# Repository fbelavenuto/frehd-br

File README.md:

# TRS-80 FreHD BR version

### English

FreHD is a HD emulator for TRS-80 classic computer.

This board is my version made in Cadsoft Eagle software. Original project:

http://members.iinet.net.au/~ianmav/trs80/emulator.htm

`FreHD` is the project itself, `CP300_Adapter` is for Brazilian TRS-80 Model III clone

### Português

FreHD é um emulador de HD para computadores TRS-80.

Estas placas são uma versão minha feito no software Autodesk Eagle. Projeto original:

http://members.iinet.net.au/~ianmav/trs80/emulator.htm

`FreHD` é o projeto em si, `CP300_Adapter` é para o clone brasileiro TRS-80 model III.

Este projeto utiliza um microcontrolador PIC que deve ser gravado com o firmware do arquivo `FreHD_213.hex` e utiliza um circuito integrado de lógica programável (GAL) que deve ser gravado com o arquivo `gal16v8.jed`.

Para o clone CP500 é necessário a regravação da EPROM interna ou troca com o conteúdo do arquivo `CP500_FreHD.rom`.

Para o CP300 é necessário a construção do adaptador que contém uma EPROM que deve ser gravada com o conteúdo do arquivo `FreHD(3000).bin`. A EPROM utilizada é a 2732 que tem espaço para 4KBytes de dados, por ser mais fácil de se encontrar. O arquivo contém somente 2KBytes de dados e deve ser gravado no começo da EPROM (offset 0) deixando o restante da EPROM sem conteúdo.

A lista de material pode ser encontrada em formato Markdown na pasta *Doc* de cada projeto.

É necessário a confecção de um cabo multivias com 50 vias/conector 2x25 para ligação entre o FreHD e Micro (ou Adaptador) e um cabo multivias de 34 vias/conector 2x17 para a ligação do adaptador no CP300. O cabo de 50 vias pode ser aproveitado de antigos cabos SCSI e para o cabo de 34 vias pode ser aproveitado cabos de floppy sem a torção.

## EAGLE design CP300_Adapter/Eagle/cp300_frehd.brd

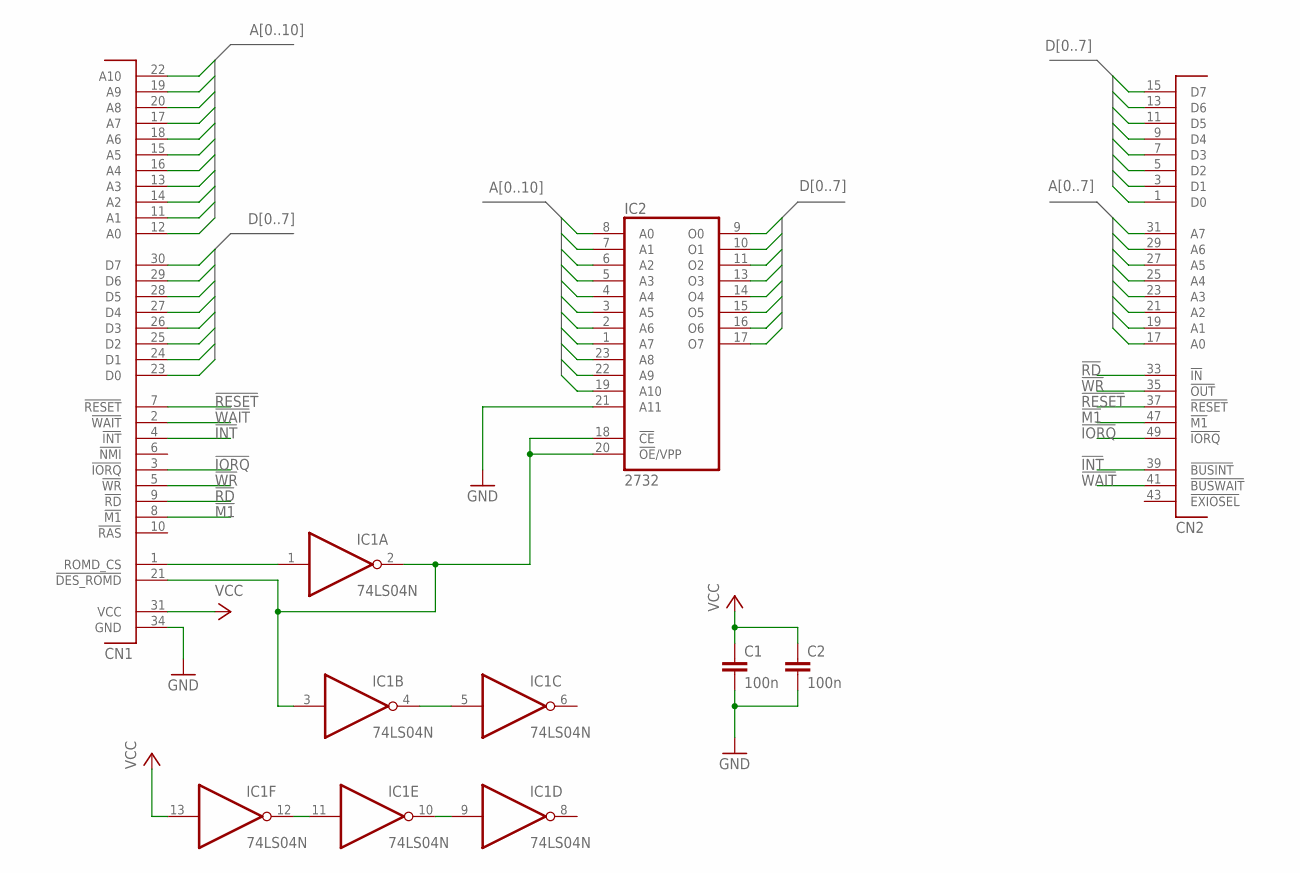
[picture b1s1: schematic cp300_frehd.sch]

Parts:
C1, C2: 100n; C050-024X044
CN1: CP300_EXPA; 2X17
CN2: TRS80_EXPA; 2X25
IC1: 74LS04N; DIL14
IC2: 2732; DIL24

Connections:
!INT: CN1.4 (!INT), CN2.39 (!BUSINT)
!IORQ: CN1.3 (!IORQ), CN2.49 (!IORQ)
!M1: CN1.8 (!M1), CN2.47 (!M1)
!RD: CN1.9 (!RD), CN2.33 (!IN)
!RESET: CN1.7 (!RESET), CN2.37 (!RESET)
!WAIT: CN1.2 (!WAIT), CN2.41 (!BUSWAIT)
!WR: CN1.5 (!WR), CN2.35 (!OUT)
A0: CN1.12 (A0), CN2.17 (A0), IC2.8 (A0)
A1: CN1.11 (A1), CN2.19 (A1), IC2.7 (A1)
A2: CN1.14 (A2), CN2.21 (A2), IC2.6 (A2)
A3: CN1.13 (A3), CN2.23 (A3), IC2.5 (A3)
A4: CN1.16 (A4), CN2.25 (A4), IC2.4 (A4)
A5: CN1.15 (A5), CN2.27 (A5), CN2.29 (A6), IC2.3 (A5)
A6: CN1.18 (A6), IC2.2 (A6)
A7: CN1.17 (A7), CN2.31 (A7), IC2.1 (A7)
A8: CN1.20 (A8), IC2.23 (A8)
A9: CN1.19 (A9), IC2.22 (A9)
A10: CN1.22 (A10), IC2.19 (A10)
D0: CN1.23 (D0), CN2.1 (D0), IC2.9 (O0)
D1: CN1.24 (D1), CN2.3 (D1), IC2.10 (O1)
D2: CN1.25 (D2), CN2.5 (D2), IC2.11 (O2)
D3: CN1.26 (D3), CN2.7 (D3), IC2.13 (O3)
D4: CN1.27 (D4), CN2.9 (D4), IC2.14 (O4)
D5: CN1.28 (D5), CN2.11 (D5), IC2.15 (O5)
D6: CN1.29 (D6), CN2.13 (D6), IC2.16 (O6)
D7: CN1.30 (D7), CN2.15 (D7), IC2.17 (O7)
GND: C1.2, C2.2, CN1.34 (GND), CN2.2 (GND), CN2.4 (GND), CN2.6 (GND), CN2.8 (GND), CN2.10 (GND), CN2.12 (GND), CN2.14 (GND), CN2.16 (GND), CN2.18 (GND), CN2.20 (GND), CN2.22 (GND), CN2.24 (GND), CN2.26 (GND), CN2.28 (GND), CN2.30 (GND), CN2.32 (GND), CN2.34 (GND), CN2.36 (GND), CN2.38 (GND), CN2.40 (GND), CN2.42 (GND), CN2.44 (GND), CN2.46 (GND), CN2.48 (GND), CN2.50 (GND), IC1.7 (GND), IC2.12 (GND), IC2.21 (A11)
unnamed: IC1.11 (I), IC1.12 (O)
unnamed: IC1.9 (I), IC1.10 (O)
unnamed: IC1.4 (O), IC1.5 (I)
unnamed: CN1.1 (ROMD_CS), IC1.1 (I)
unnamed: CN1.21 (!DES_ROMD), IC1.2 (O), IC1.3 (I), IC2.18 (!CE), IC2.20 (!OE!/VPP)
VCC: C1.1, C2.1, CN1.31 (VCC), IC1.13 (I), IC1.14 (VCC), IC2.24 (VCC)

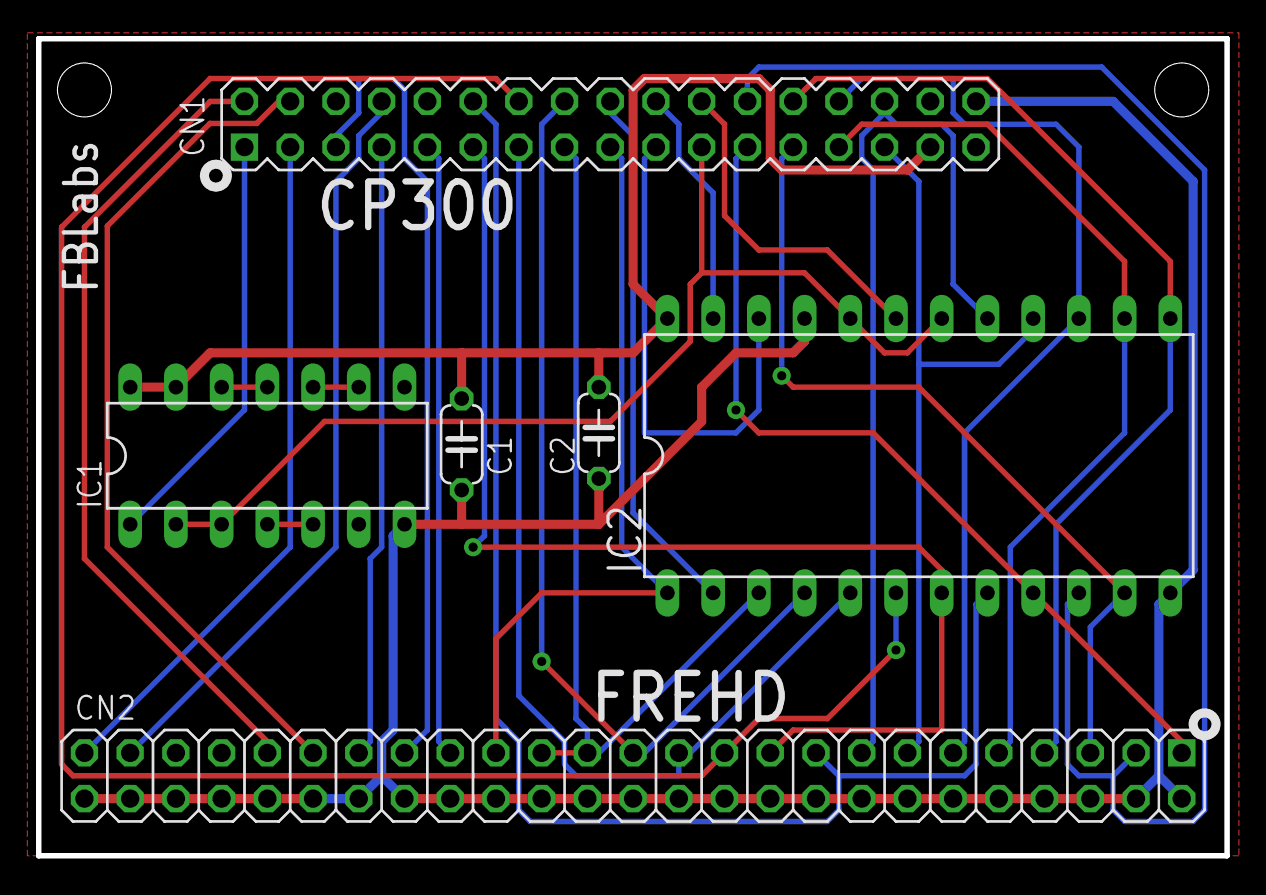
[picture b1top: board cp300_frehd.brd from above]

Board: 2 copper layers, 66.0 x 45.4 mm, 6 parts (0 on the bottom side), 33 nets.

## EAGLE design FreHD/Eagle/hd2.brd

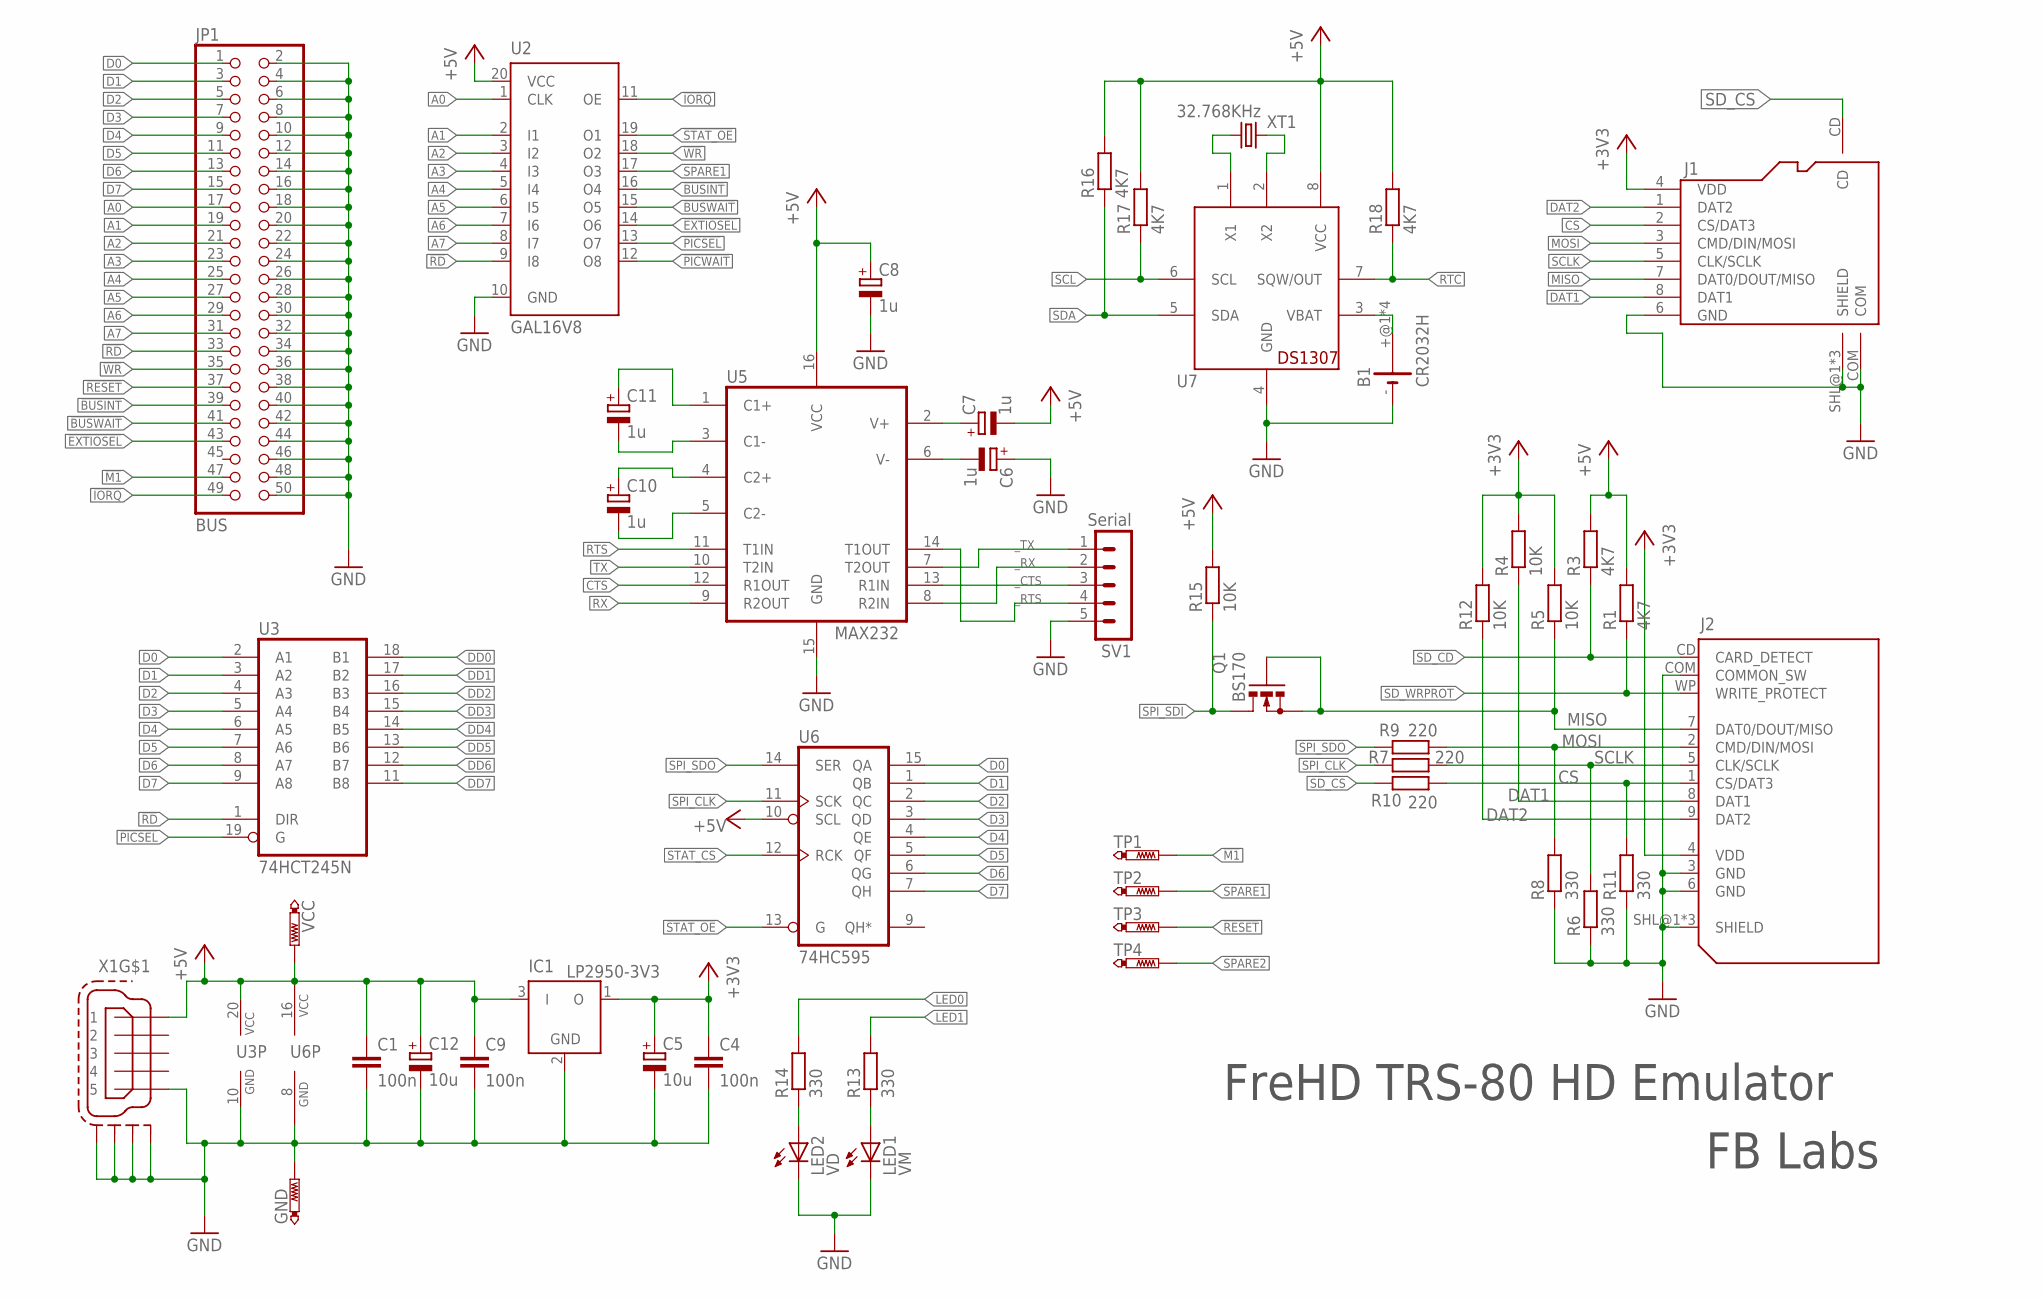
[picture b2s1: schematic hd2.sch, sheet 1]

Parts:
B1: CR2032H
C1, C4, C9: 100n; C050-024X044
C5, C12: 10u; E2-4
C6, C7, C8, C10, C11: 1u; E2-4
GND: PTR1B2,54; B2,54
IC1: LP2950-3V3; TO92
J1: MICROSD-9P; 9P-SMD-W/-RING
J2: SDMMC06132; 06132
JP1: BUS; 2X25
LED1: VM; LED3MM
LED2: VD; LED3MM
Q1: BS170; SOT54E
R1, R3, R16, R17, R18: 4K7; 0207/10
R4, R5, R12, R15: 10K; 0207/10
R6, R8, R11, R13, R14: 330; 0207/10
R7, R9, R10: 220; 0207/10
SV1: Serial; MA05-1
TP1, TP2, TP3, TP4: PTR1PAD1-10; P1-10
U2: GAL16V8; DIL20
U3: 74HCT245N; DIL20
U5: MAX232; DIL16
U6: 74HC595; DIL16
U7: DS1307; DIL08
VCC: PTR1B2,54; B2,54
X1: MINI-USB-SCHIELD-32005-301; 32005-301
XT1: 32.768KHz; TC26V

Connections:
!BUSINT: JP1.39, U2.16 (O4)
!BUSWAIT: JP1.41, U2.15 (O5)
!EXTIOSEL: JP1.43, U2.14 (O6)
!IORQ: JP1.49, U2.11 (OE)
!M1: JP1.47, TP1.TP
!PICSEL: U2.13 (O7), U3.19 (G); also elsewhere on the board
!PICWAIT: U2.12 (O8); also elsewhere on the board
!RD: JP1.33, U2.9 (I8), U3.1 (DIR); also elsewhere on the board
!RESET: JP1.37, TP3.TP
!STAT_OE: U2.19 (O1), U6.13 (G)
!WR: JP1.35, U2.18 (O2)
+3V3: C4.1, C5.+, IC1.1 (O), J1.4 (VDD), J2.4 (VDD), R4.2, R5.2, R12.2
+5V: C1.1, C7.-, C8.+, C9.1, C12.+, IC1.3 (I), R1.2, R3.2, R15.2, R16.2, R17.2, R18.2, U2.20 (VCC), U3.20 (VCC), U5.16 (VCC), U6.10 (SCL), U6.16 (VCC), U7.8 (VCC), VCC.TP, X1.1; also elsewhere on the board
A0: JP1.17, U2.1 (CLK); also elsewhere on the board
A1: JP1.19, U2.2 (I1); also elsewhere on the board
A2: JP1.21, U2.3 (I2); also elsewhere on the board
A3: JP1.23, U2.4 (I3); also elsewhere on the board
A4: JP1.25, U2.5 (I4)
A5: JP1.27, U2.6 (I5)
A6: JP1.29, U2.7 (I6)
A7: JP1.31, U2.8 (I7)
CS: J1.2 (CS/DAT3), J2.1 (CS/DAT3), R10.1, R11.2
CTS: U5.12 (R1OUT); also elsewhere on the board
D0: JP1.1, U3.2 (A1), U6.15 (QA)
D1: JP1.3, U3.3 (A2), U6.1 (QB)
D2: JP1.5, U3.4 (A3), U6.2 (QC)
D3: JP1.7, U3.5 (A4), U6.3 (QD)
D4: JP1.9, U3.6 (A5), U6.4 (QE)
D5: JP1.11, U3.7 (A6), U6.5 (QF)
D6: JP1.13, U3.8 (A7), U6.6 (QG)
D7: JP1.15, U3.9 (A8), U6.7 (QH)
DAT1: J1.8 (DAT1), J2.8 (DAT1), R4.1
DAT2: J1.1 (DAT2), J2.9 (DAT2), R12.1
DD0: U3.18 (B1); also elsewhere on the board
DD1: U3.17 (B2); also elsewhere on the board
DD2: U3.16 (B3); also elsewhere on the board
DD3: U3.15 (B4); also elsewhere on the board
DD4: U3.14 (B5); also elsewhere on the board
DD5: U3.13 (B6); also elsewhere on the board
DD6: U3.12 (B7); also elsewhere on the board
DD7: U3.11 (B8); also elsewhere on the board
GND: B1.-, C1.2, C4.2, C5.-, C6.+, C8.-, C9.2, C12.-, GND.TP, IC1.2 (GND), J1.6 (GND), J1.COM, J1.SHL@1 (SHIELD), J1.SHL@2 (SHIELD), J1.SHL@3 (SHIELD), J2.3 (GND), J2.6 (GND), J2.COM (COMMON_SW), J2.SHL@1 (SHIELD), J2.SHL@2 (SHIELD), J2.SHL@3 (SHIELD), JP1.2, JP1.4, JP1.6, JP1.8, JP1.10, JP1.12, JP1.14, JP1.16, JP1.18, JP1.20, JP1.22, JP1.24, JP1.26, JP1.28, JP1.30, JP1.32, JP1.34, JP1.36, JP1.38, JP1.40, JP1.42, JP1.44, JP1.46, JP1.48, JP1.50, LED1.K (C), LED2.K (C), R6.1, R8.1, R11.1, SV1.5, U2.10 (GND), U3.10 (GND), U5.15 (GND), U6.8 (GND), U7.4 (GND), X1.5, X1.M1 (S1), X1.M2 (S2), X1.M3 (S3), X1.M4 (S4); also elsewhere on the board
LED0: R14.2; also elsewhere on the board
LED1: R13.2; also elsewhere on the board
MISO: J1.7 (DAT0/DOUT/MISO), J2.7 (DAT0/DOUT/MISO), Q1.G, Q1.S, R5.1
MOSI: J1.3 (CMD/DIN/MOSI), J2.2 (CMD/DIN/MOSI), R8.2, R9.1
unnamed: U7.1 (X1), XT1.1
unnamed: U7.2 (X2), XT1.2
unnamed: C6.-, U5.6 (V-)
unnamed: C7.+, U5.2 (V+)
unnamed: B1.+@1 (+), B1.+@2 (+), B1.+@3 (+), B1.+@4 (+), U7.3 (VBAT)
unnamed: C11.-, U5.3 (C1-)
unnamed: C11.+, U5.1 (C1+)
unnamed: C10.+, U5.4 (C2+)
unnamed: C10.-, U5.5 (C2-)
unnamed: LED2.A, R14.1
unnamed: LED1.A, R13.1
RTC: R18.1, U7.7 (SQW/OUT); also elsewhere on the board
RTS: U5.11 (T1IN); also elsewhere on the board
RX: U5.9 (R2OUT); also elsewhere on the board
SCL: R17.1, U7.6 (SCL); also elsewhere on the board
SCLK: J1.5 (CLK/SCLK), J2.5 (CLK/SCLK), R6.2, R7.1
SDA: R16.1, U7.5 (SDA); also elsewhere on the board
SD_CD: J2.CD (CARD_DETECT), R3.1; also elsewhere on the board
SD_CS: J1.CD, R10.2; also elsewhere on the board
SD_WRPROT: J2.WP (WRITE_PROTECT), R1.1; also elsewhere on the board
SPARE1: TP2.TP, U2.17 (O3); also elsewhere on the board
SPARE2: TP4.TP; also elsewhere on the board
SPI_CLK: R7.2, U6.11 (SCK); also elsewhere on the board
SPI_SDI: Q1.D, R15.1; also elsewhere on the board
SPI_SDO: R9.2, U6.14 (SER); also elsewhere on the board
STAT_CS: U6.12 (RCK); also elsewhere on the board
TX: U5.10 (T2IN); also elsewhere on the board
_CTS: SV1.3, U5.13 (R1IN)
_RTS: SV1.4, U5.14 (T1OUT)
_RX: SV1.2, U5.8 (R2IN)
_TX: SV1.1, U5.7 (T2OUT)

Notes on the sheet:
FreHD TRS-80 HD Emulator
FB Labs

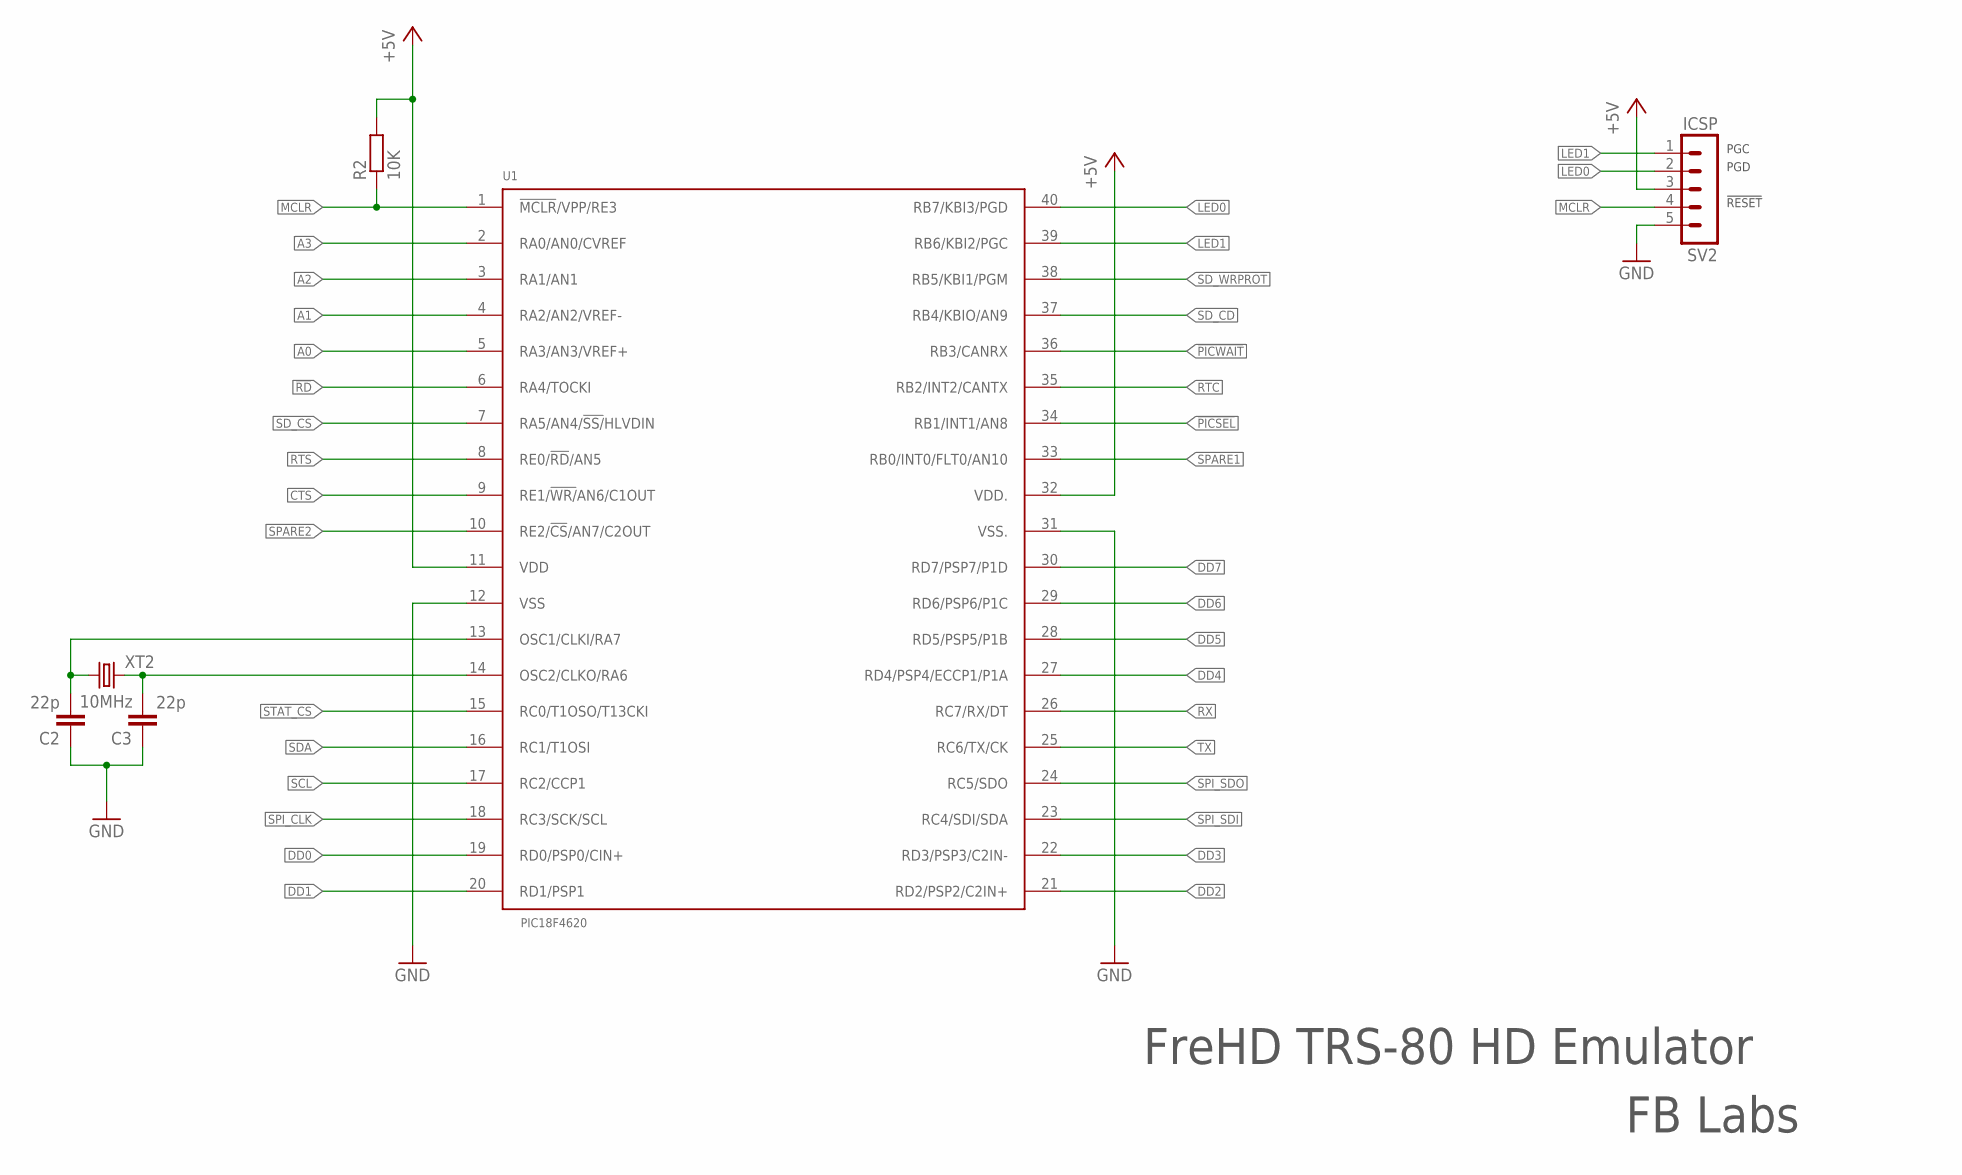
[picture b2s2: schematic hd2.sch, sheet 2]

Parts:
C2, C3: 22p; C050-024X044
R2: 10K; 0207/10
SV2: ICSP; MA05-1
U1: PIC18F4620; PDIP-40
XT2: 10MHz; HC49U-V

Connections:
!PICSEL: U1.34 (RB1/INT1/AN8); also elsewhere on the board
!PICWAIT: U1.36 (RB3/CANRX); also elsewhere on the board
!RD: U1.6 (RA4/TOCKI); also elsewhere on the board
+5V: R2.2, SV2.3, U1.11 (VDD), U1.32 (VDD.); also elsewhere on the board
A0: U1.5 (RA3/AN3/VREF+); also elsewhere on the board
A1: U1.4 (RA2/AN2/VREF-); also elsewhere on the board
A2: U1.3 (RA1/AN1); also elsewhere on the board
A3: U1.2 (RA0/AN0/CVREF); also elsewhere on the board
CTS: U1.9 (RE1/!WR/!AN6/C1OUT); also elsewhere on the board
DD0: U1.19 (RD0/PSP0/CIN+); also elsewhere on the board
DD1: U1.20 (RD1/PSP1); also elsewhere on the board
DD2: U1.21 (RD2/PSP2/C2IN+); also elsewhere on the board
DD3: U1.22 (RD3/PSP3/C2IN-); also elsewhere on the board
DD4: U1.27 (RD4/PSP4/ECCP1/P1A); also elsewhere on the board
DD5: U1.28 (RD5/PSP5/P1B); also elsewhere on the board
DD6: U1.29 (RD6/PSP6/P1C); also elsewhere on the board
DD7: U1.30 (RD7/PSP7/P1D); also elsewhere on the board
GND: C2.1, C3.1, SV2.5, U1.12 (VSS), U1.31 (VSS.); also elsewhere on the board
LED0: SV2.2, U1.40 (RB7/KBI3/PGD); also elsewhere on the board
LED1: SV2.1, U1.39 (RB6/KBI2/PGC); also elsewhere on the board
MCLR: R2.1, SV2.4, U1.1 (!MCLR!/VPP/RE3)
unnamed: C2.2, U1.13 (OSC1/CLKI/RA7), XT2.1
unnamed: C3.2, U1.14 (OSC2/CLKO/RA6), XT2.2
RTC: U1.35 (RB2/INT2/CANTX); also elsewhere on the board
RTS: U1.8 (RE0/!RD!/AN5); also elsewhere on the board
RX: U1.26 (RC7/RX/DT); also elsewhere on the board
SCL: U1.17 (RC2/CCP1); also elsewhere on the board
SDA: U1.16 (RC1/T1OSI); also elsewhere on the board
SD_CD: U1.37 (RB4/KBIO/AN9); also elsewhere on the board
SD_CS: U1.7 (RA5/AN4/!SS/!HLVDIN); also elsewhere on the board
SD_WRPROT: U1.38 (RB5/KBI1/PGM); also elsewhere on the board
SPARE1: U1.33 (RB0/INT0/FLT0/AN10); also elsewhere on the board
SPARE2: U1.10 (RE2/!CS!/AN7/C2OUT); also elsewhere on the board
SPI_CLK: U1.18 (RC3/SCK/SCL); also elsewhere on the board
SPI_SDI: U1.23 (RC4/SDI/SDA); also elsewhere on the board
SPI_SDO: U1.24 (RC5/SDO); also elsewhere on the board
STAT_CS: U1.15 (RC0/T1OSO/T13CKI); also elsewhere on the board
TX: U1.25 (RC6/TX/CK); also elsewhere on the board

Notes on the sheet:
PGD
PGC
!RESET
FreHD TRS-80 HD Emulator
FB Labs

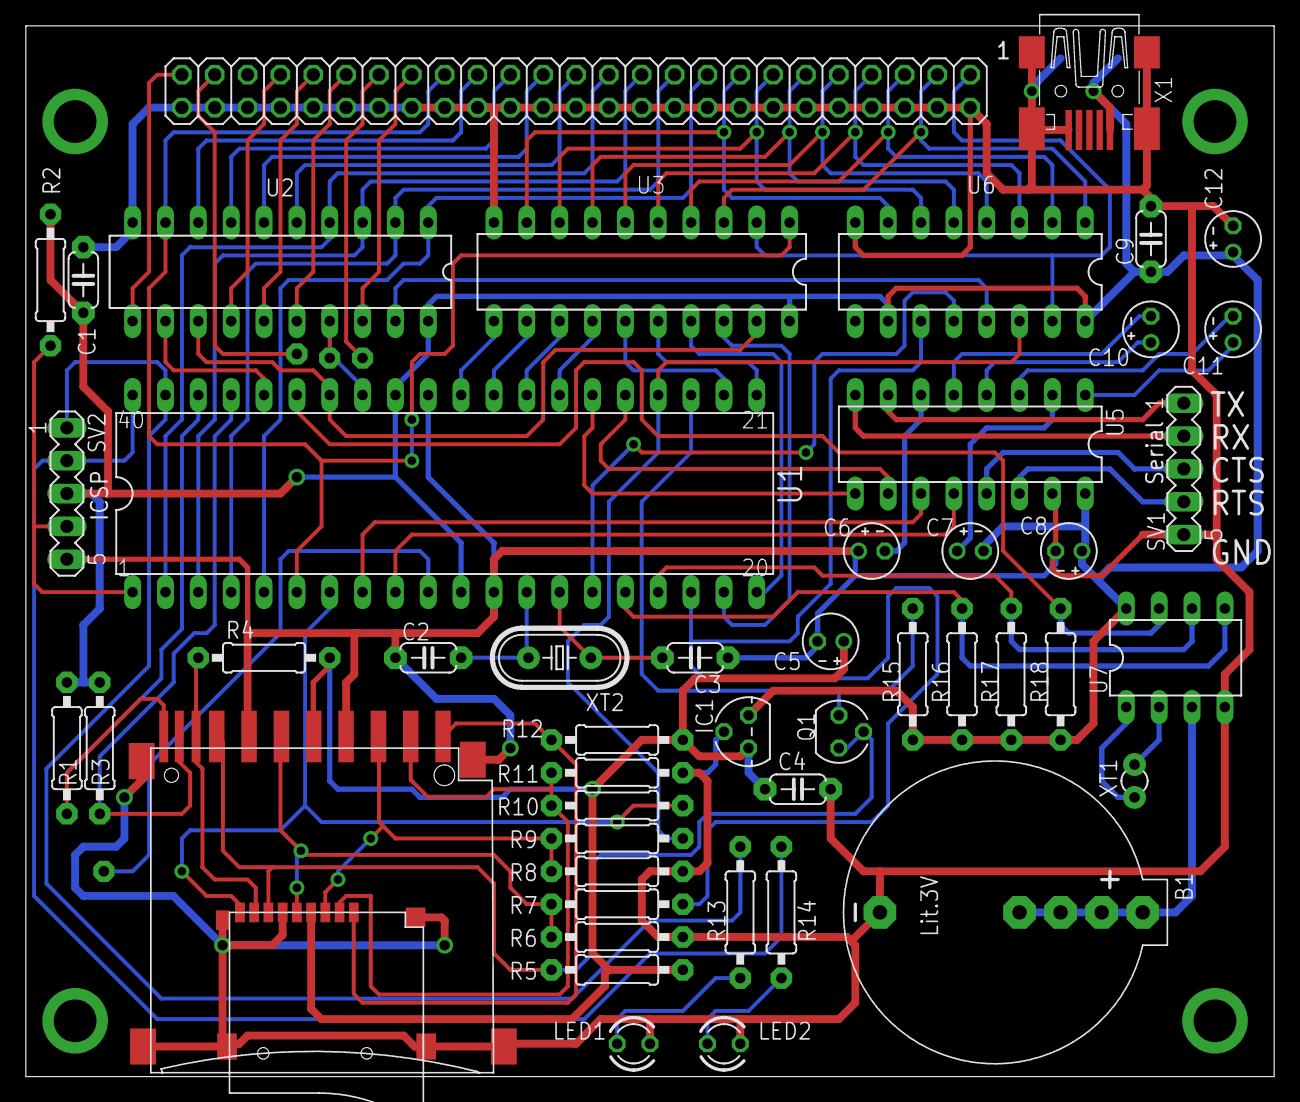
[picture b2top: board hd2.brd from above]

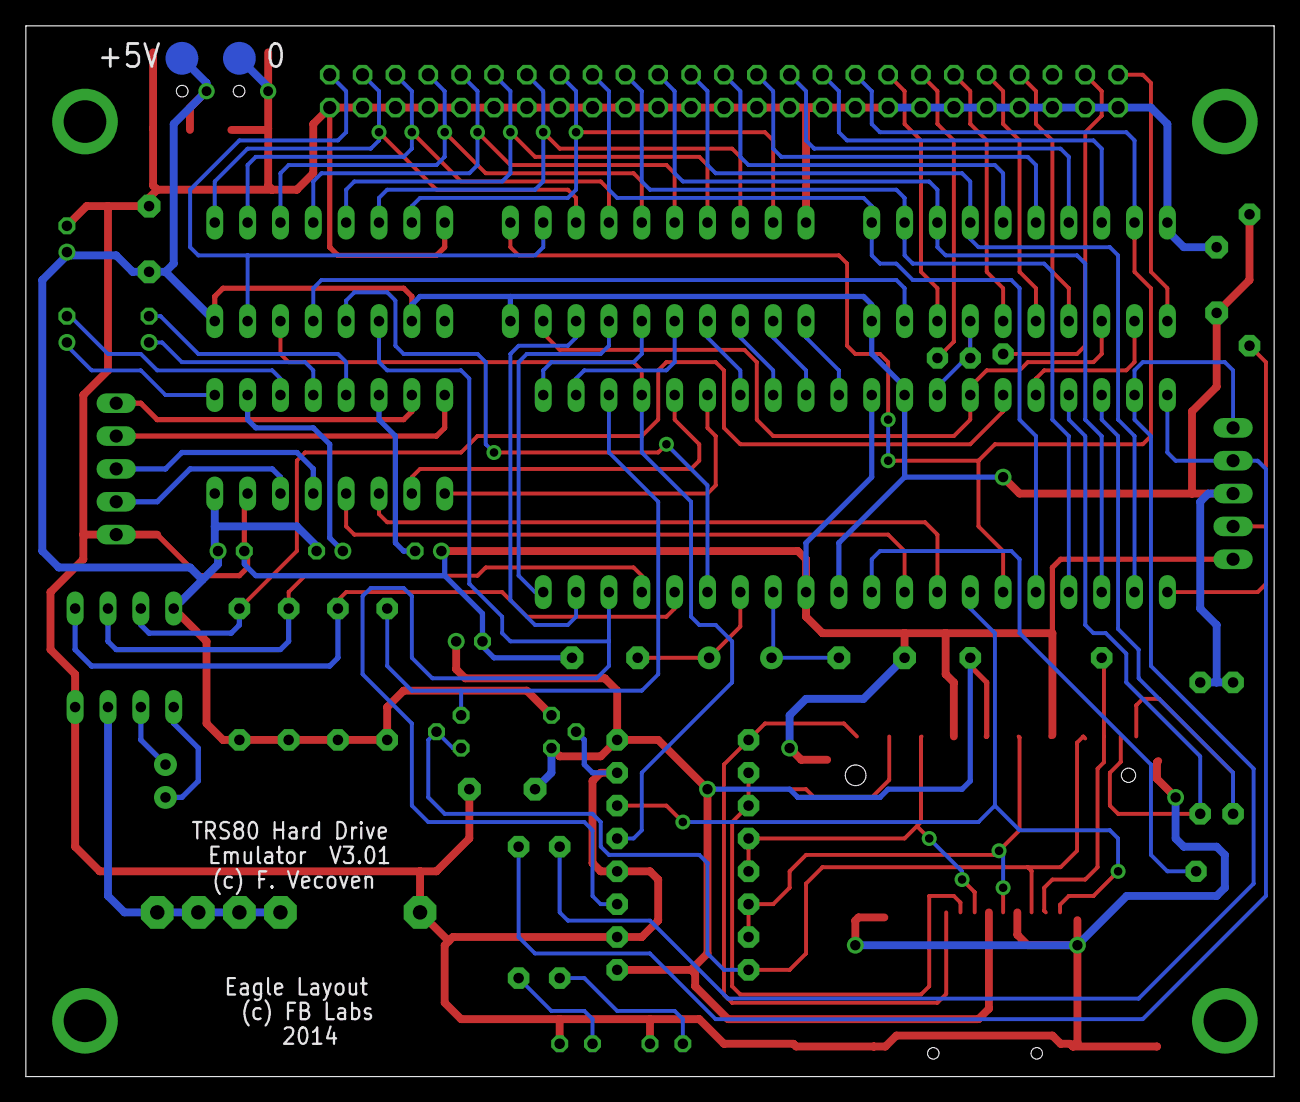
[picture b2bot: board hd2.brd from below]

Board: 2 copper layers, 96.5 x 81.2 mm, 55 parts (2 on the bottom side), 80 nets.

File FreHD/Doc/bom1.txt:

Part Value       Device          Package      Description

U1   PIC18F4620  PIC18F4680      PDIP-40
U2   GAL16V8     ATF16V8BP3      DIL20        High perfomance CMOS (electrically erasable) programmable logic device (PLD)
U3   74HCT245N   74HCT245N       DIL20        Octal BUS TRANSCEIVER, 3-state
U5   MAX232      MAX232PTH       DIL16        RS232 Transceiver
U6   74HC595N    74HC595N        DIL16        8-bit SHIFT REGISTER, output latch
U7   DS1307      DS1307          DIL08        DS1307
IC1  LP2950-3V3  LP2950Z         TO92         100 mA, Low Power Low Dropout Voltage Regulator
Q1   BS170       BS170           SOT54E       N-CHANNEL MOS FET
J1   MICROSD     MICROSD         MICROSD      Micro SD Socket (optional)
J2   SDMMC06132  SDMMC06132      06132        SD MMC Card holder
XT1  32.768KHz   CRYSTALTC26V    TC26V        CRYSTAL
XT2  10MHz       CRYSTALHC49U-V  HC49U-V      CRYSTAL
B1   CR2032H     CR2032H         CR2032H      LI BATTERY Varta
C1   100n        C-EU050-024X044 C050-024X044 CAPACITOR, European symbol
C2   22p         C-EU050-024X044 C050-024X044 CAPACITOR, European symbol
C3   22p         C-EU050-024X044 C050-024X044 CAPACITOR, European symbol
C4   100n        C-EU050-024X044 C050-024X044 CAPACITOR, European symbol
C5   10u         CPOL-EUE2-4     E2-4         POLARIZED CAPACITOR, European symbol
C6   1u          CPOL-EUE2-4     E2-4         POLARIZED CAPACITOR, European symbol
C7   1u          CPOL-EUE2-4     E2-4         POLARIZED CAPACITOR, European symbol
C8   1u          CPOL-EUE2-4     E2-4         POLARIZED CAPACITOR, European symbol
C9   100n        C-EU050-024X044 C050-024X044 CAPACITOR, European symbol
C10  1u          CPOL-EUE2-4     E2-4         POLARIZED CAPACITOR, European symbol
C11  1u          CPOL-EUE2-4     E2-4         POLARIZED CAPACITOR, European symbol
C12  10u         CPOL-EUE2-4     E2-4         POLARIZED CAPACITOR, European symbol
R1   4K7         R-EU_0207/10    0207/10      RESISTOR, European symbol
R2   10K         R-EU_0207/10    0207/10      RESISTOR, European symbol
R3   4K7         R-EU_0207/10    0207/10      RESISTOR, European symbol
R4   10K         R-EU_0207/10    0207/10      RESISTOR, European symbol
R5   10K         R-EU_0207/10    0207/10      RESISTOR, European symbol
R6   330         R-EU_0207/10    0207/10      RESISTOR, European symbol
R7   220         R-EU_0207/10    0207/10      RESISTOR, European symbol
R8   330         R-EU_0207/10    0207/10      RESISTOR, European symbol
R9   220         R-EU_0207/10    0207/10      RESISTOR, European symbol
R10  220         R-EU_0207/10    0207/10      RESISTOR, European symbol
R11  330         R-EU_0207/10    0207/10      RESISTOR, European symbol
R12  10K         R-EU_0207/10    0207/10      RESISTOR, European symbol
R13  330         R-EU_0207/10    0207/10      RESISTOR, European symbol
R14  330         R-EU_0207/10    0207/10      RESISTOR, European symbol
R15  10K         R-EU_0207/10    0207/10      RESISTOR, European symbol
R16  4K7         R-EU_0207/10    0207/10      RESISTOR, European symbol
R17  4K7         R-EU_0207/10    0207/10      RESISTOR, European symbol
R18  4K7         R-EU_0207/10    0207/10      RESISTOR, European symbol
X1   MUSB-B      MiniUSB type B  M-USB B      Mini USB type B connector
JP1  BUS         PINHD-2X25      2X25         PIN HEADER
SV1  Serial      MA05-1          MA05-1       PIN HEADER
SV2  ICSP        MA05-1          MA05-1       PIN HEADER
LED1 VM          LED3MM          LED3MM       LED Red 3mm
LED2 VD          LED3MM          LED3MM       LED Green 3mm

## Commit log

2021-04-29 Corrigindo gitignore e adicionado arquivos de furação Gerber
2021-05-01 Adicionado documentação e lista de materiais

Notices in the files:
parts and their libraries:
SparkFun: Licensing: CC v3.0 Share-Alike You are welcome to use this library for commercial purposes.
